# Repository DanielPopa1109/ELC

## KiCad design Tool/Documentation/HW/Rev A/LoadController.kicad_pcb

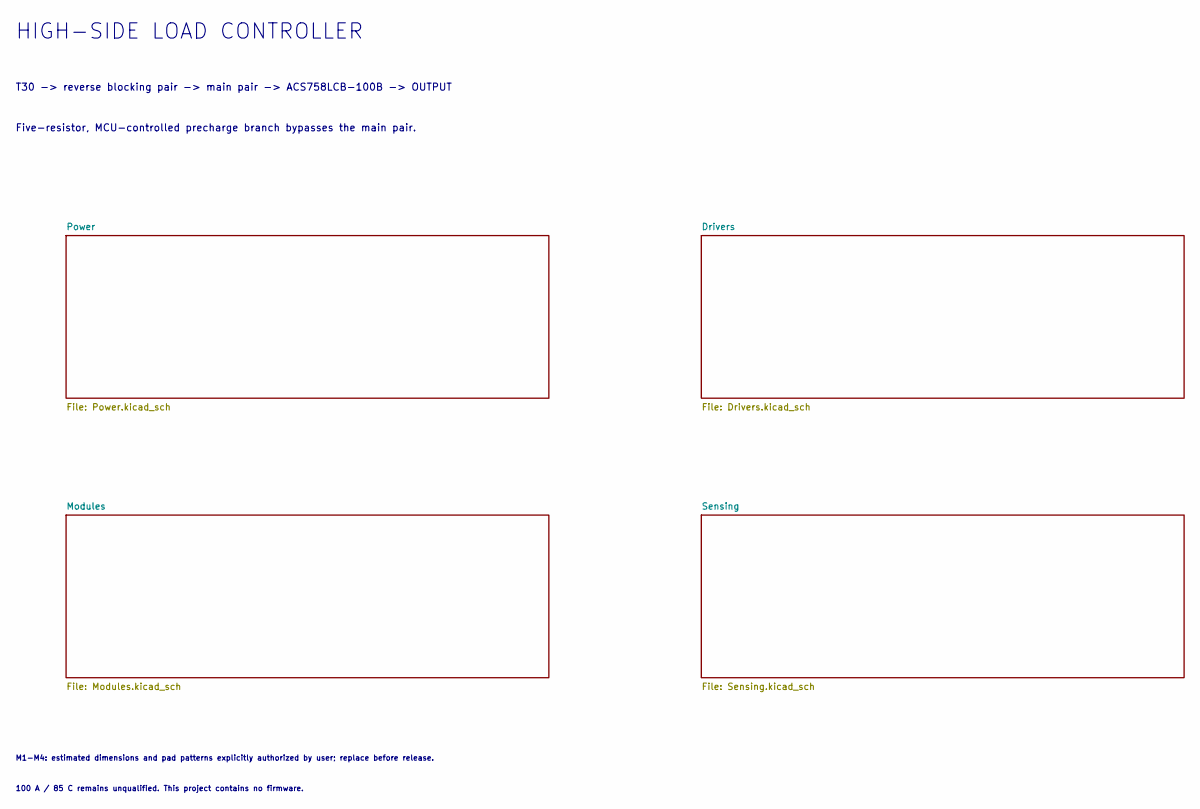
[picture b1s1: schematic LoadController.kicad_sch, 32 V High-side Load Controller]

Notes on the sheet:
Five-resistor, MCU-controlled precharge branch bypasses the main pair.
T30 -> reverse blocking pair -> main pair -> ACS758LCB-100B -> OUTPUT
100 A / 85 C remains unqualified. This project contains no firmware.
M1-M4: estimated dimensions and pad patterns explicitly authorized by user; replace before release.
HIGH-SIDE LOAD CONTROLLER

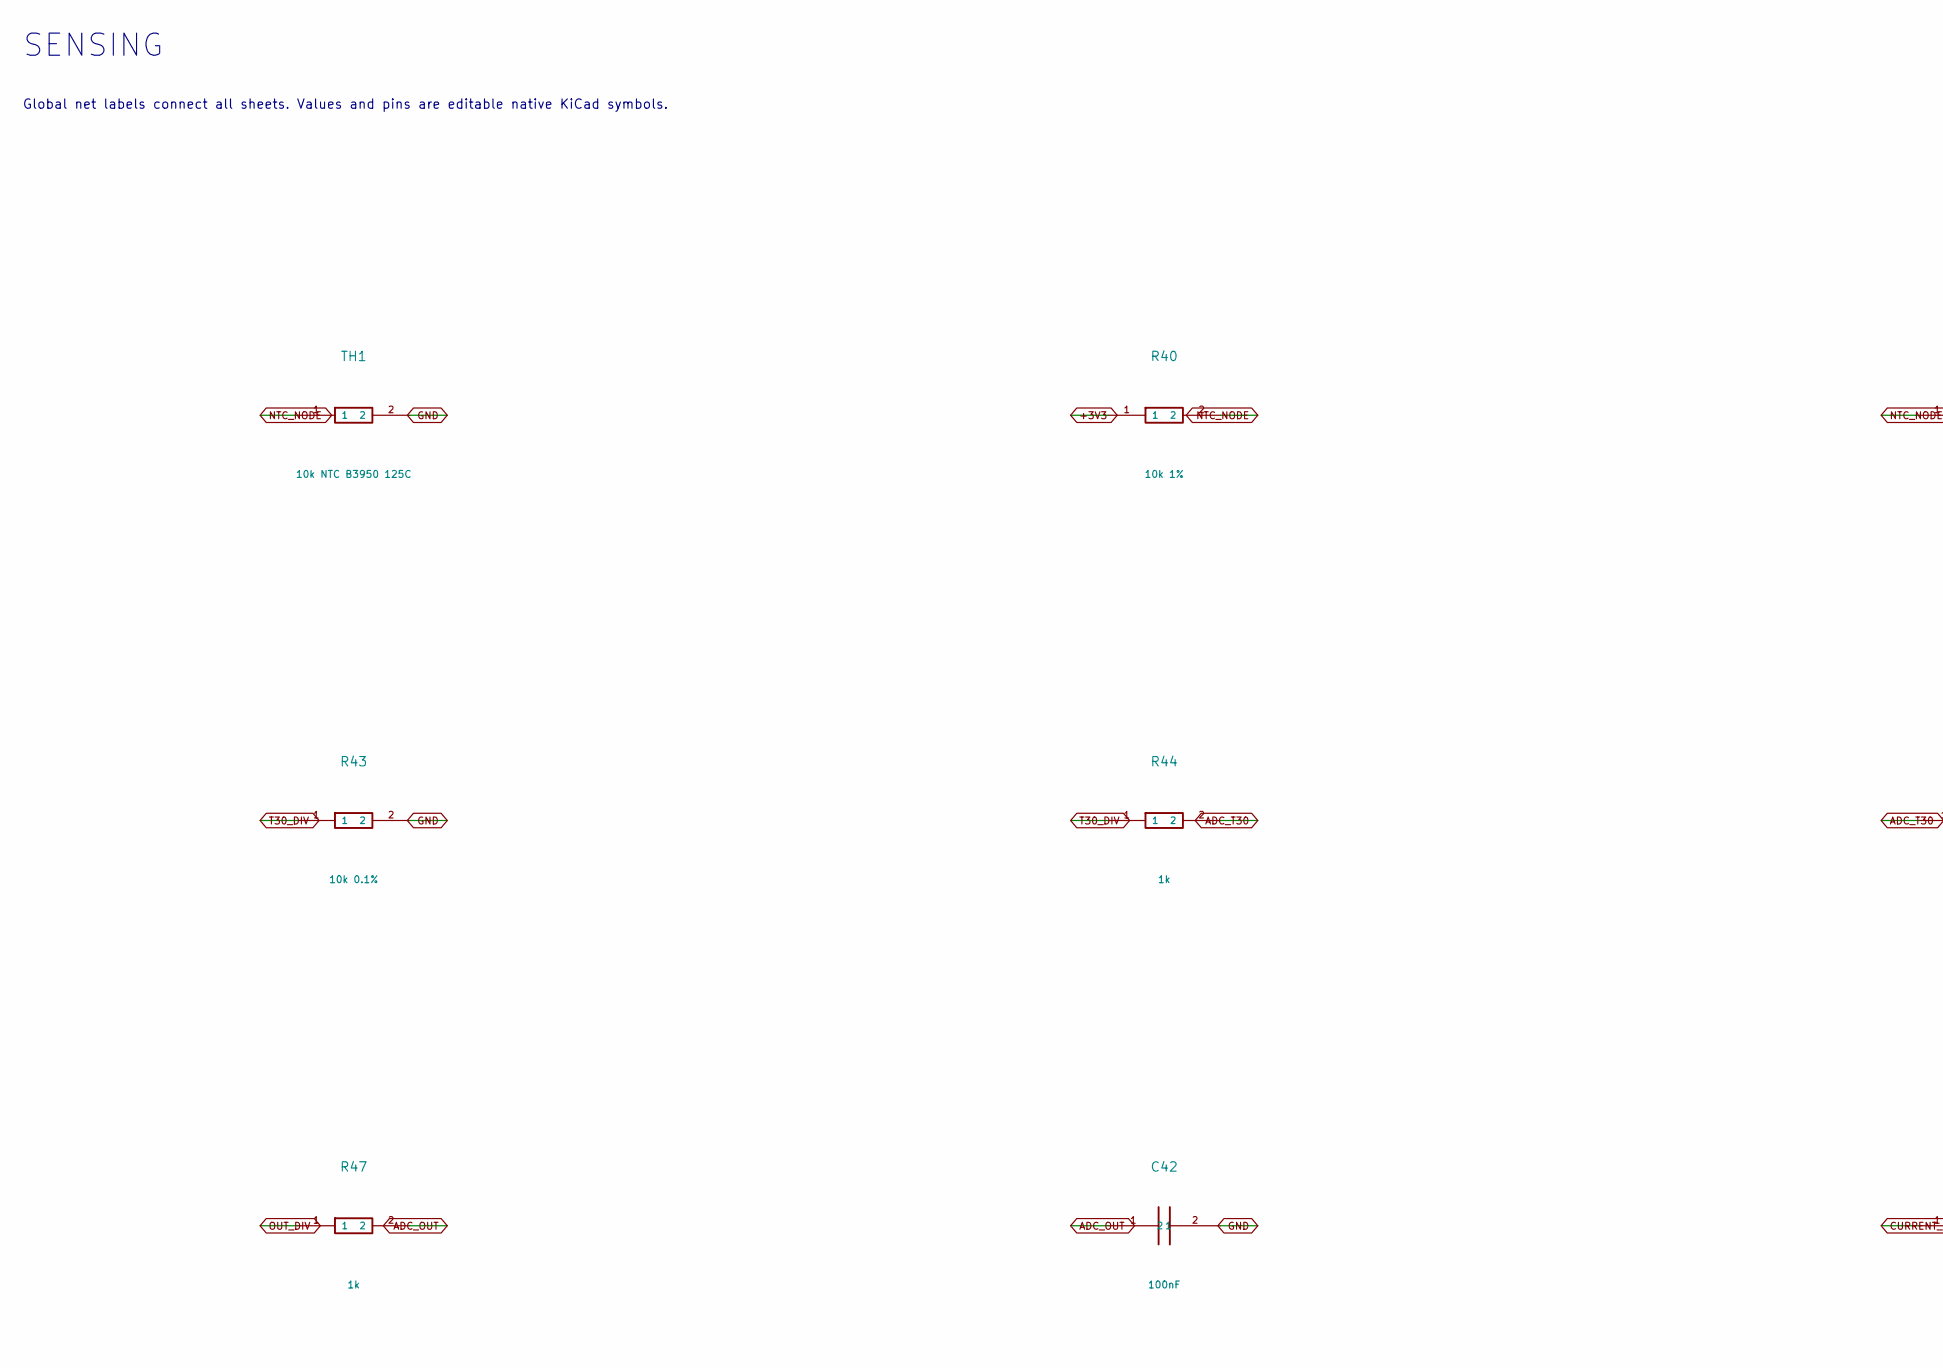
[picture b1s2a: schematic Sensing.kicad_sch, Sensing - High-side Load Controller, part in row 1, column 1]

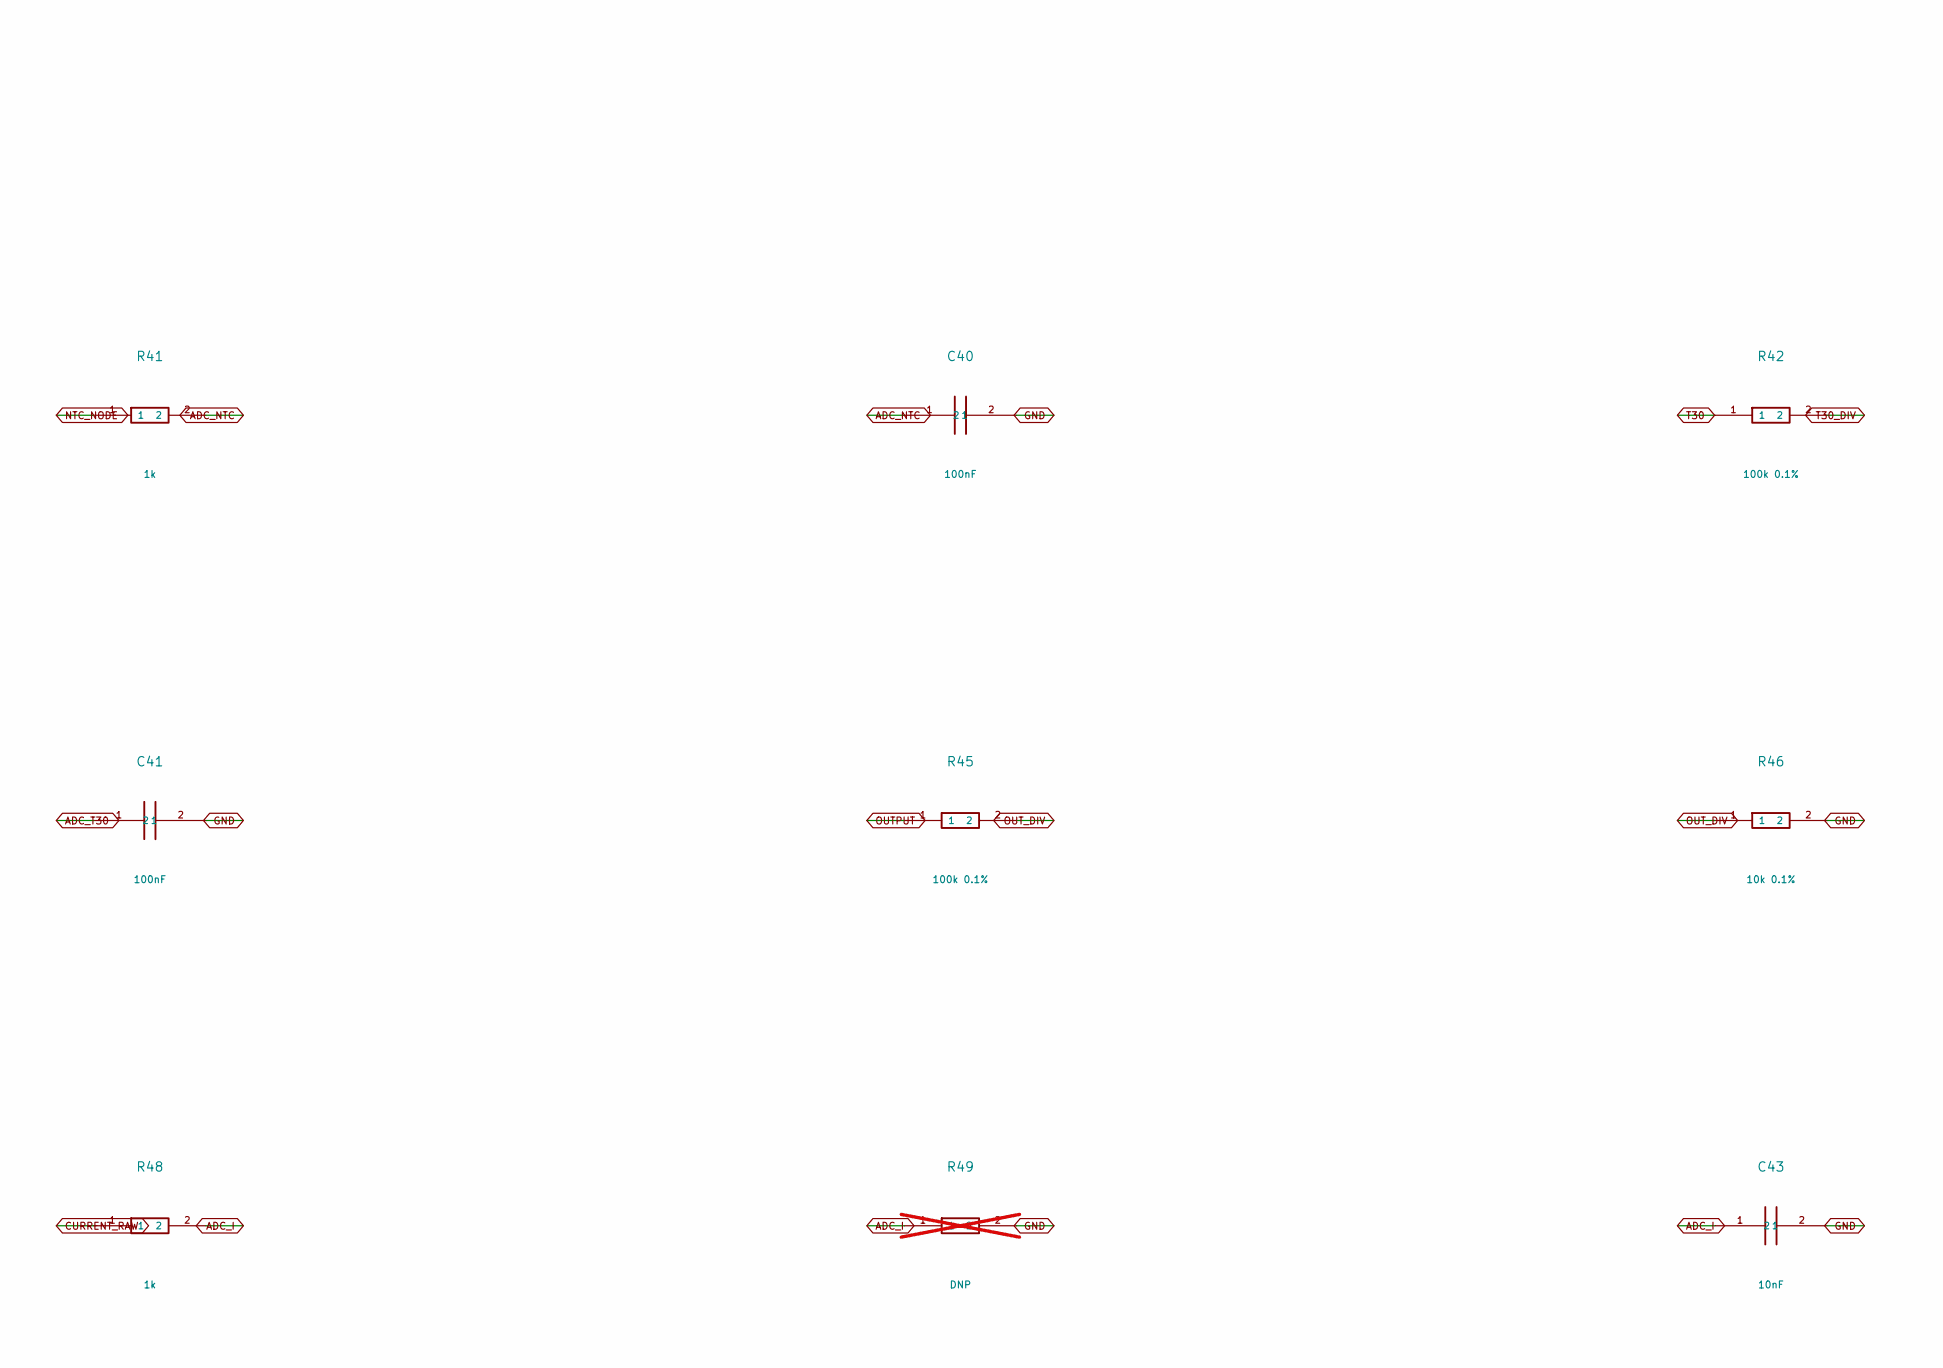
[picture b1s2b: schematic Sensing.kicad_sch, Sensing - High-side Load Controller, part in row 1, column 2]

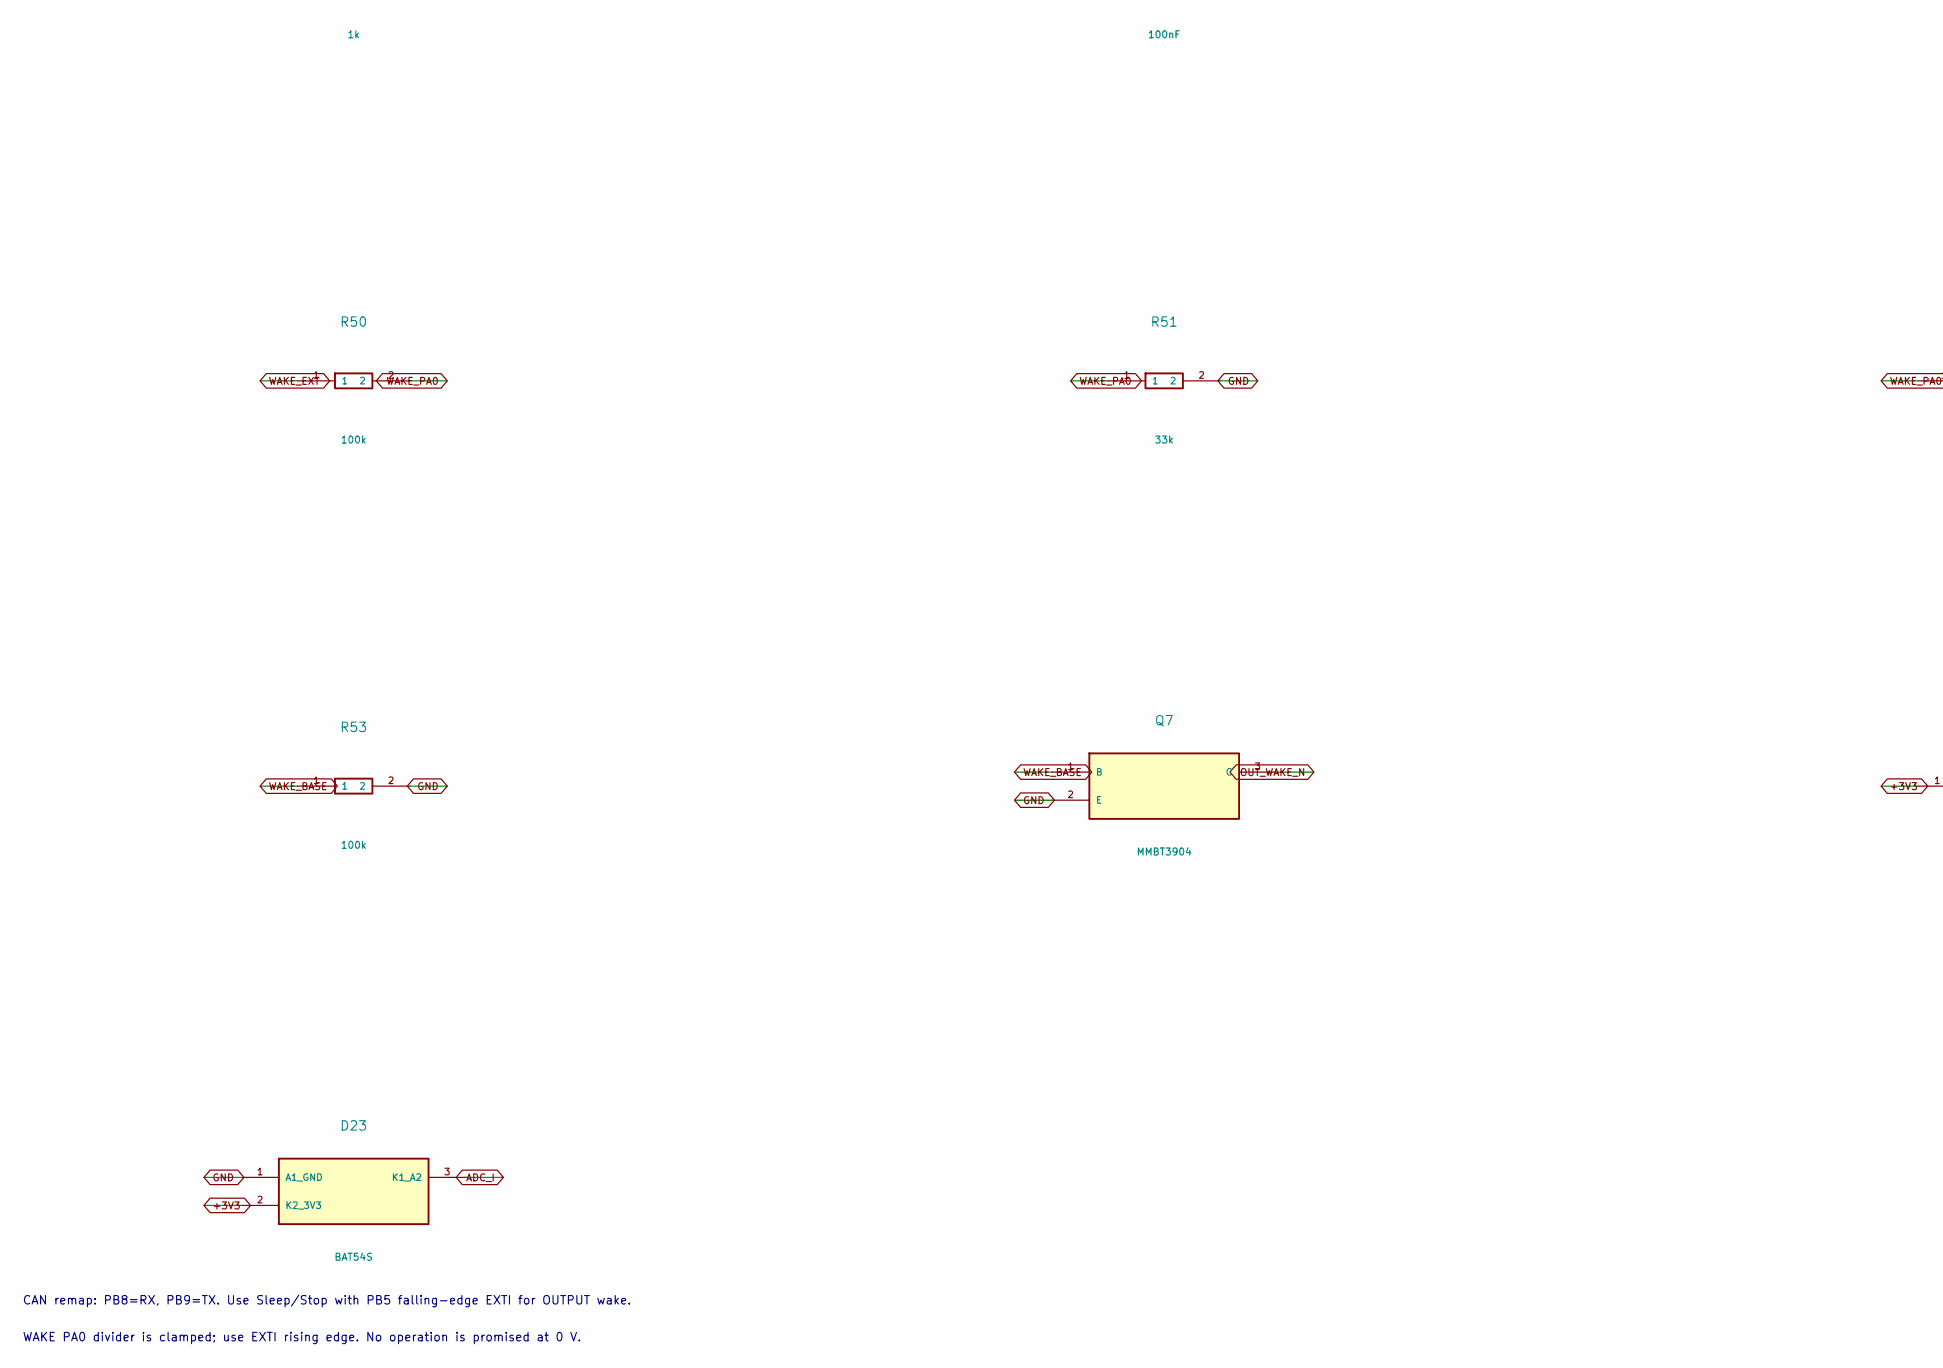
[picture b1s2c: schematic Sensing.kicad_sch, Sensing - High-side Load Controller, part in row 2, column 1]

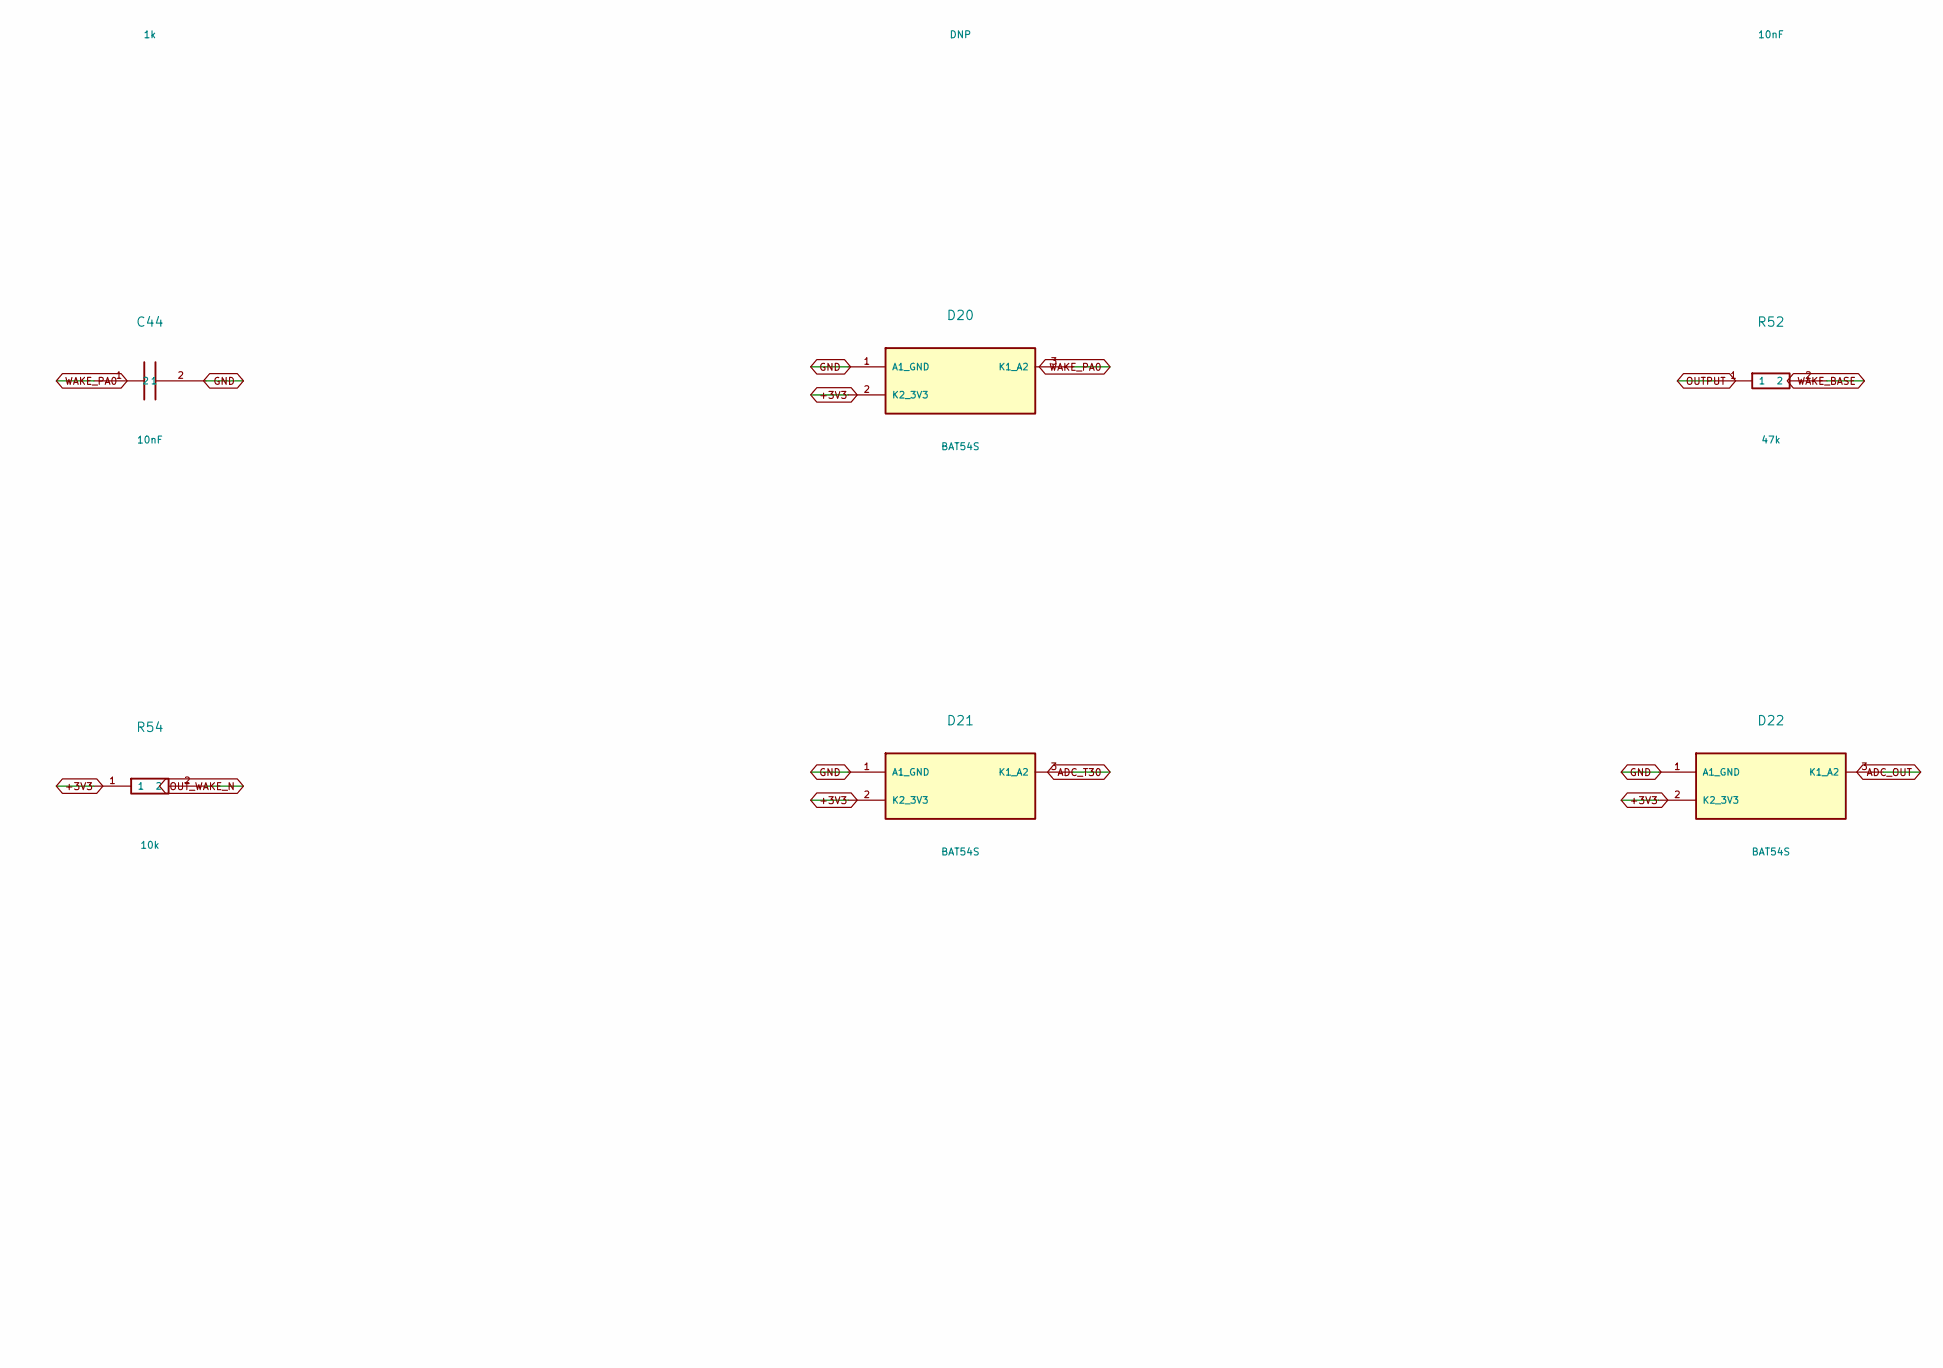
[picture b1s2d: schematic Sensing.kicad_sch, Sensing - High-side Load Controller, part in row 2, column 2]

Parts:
C40, C41, C42: 100nF; 0805
C43, C44: 10nF; 0805
D20, D21, D22, D23: BAT54S; SOT23
Q7: MMBT3904; SOT23
R40: 10k 1%; 0805
R41, R44, R47, R48: 1k; 0805
R42, R45: 100k 0.1%; 0805
R43, R46: 10k 0.1%; 0805
R49: DNP; 0805; not fitted
R50, R53: 100k; 0805
R51: 33k; 0805
R52: 47k; 0805
R54: 10k; 0805
TH1: 10k NTC B3950 125C; 0805

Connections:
+3V3: D20.2 (K2_3V3), D21.2 (K2_3V3), D22.2 (K2_3V3), D23.2 (K2_3V3), R40.1, R54.1; also elsewhere on the board
ADC_I: C43.1, D23.3 (K1_A2), R48.2, R49.1; also elsewhere on the board
ADC_NTC: C40.1, R41.2; also elsewhere on the board
ADC_OUT: C42.1, D22.3 (K1_A2), R47.2; also elsewhere on the board
ADC_T30: C41.1, D21.3 (K1_A2), R44.2; also elsewhere on the board
CURRENT_RAW: R48.1; also elsewhere on the board
GND: C40.2, C41.2, C42.2, C43.2, C44.2, D20.1 (A1_GND), D21.1 (A1_GND), D22.1 (A1_GND), D23.1 (A1_GND), Q7.2 (E), R43.2, R46.2, R49.2, R51.2, R53.2, TH1.2; also elsewhere on the board
NTC_NODE: R40.2, R41.1, TH1.1
OUTPUT: R45.1, R52.1; also elsewhere on the board
OUT_DIV: R45.2, R46.1, R47.1
OUT_WAKE_N: Q7.3 (C), R54.2; also elsewhere on the board
T30: R42.1; also elsewhere on the board
T30_DIV: R42.2, R43.1, R44.1
WAKE_BASE: Q7.1 (B), R52.2, R53.1
WAKE_EXT: R50.1; also elsewhere on the board
WAKE_PA0: C44.1, D20.3 (K1_A2), R50.2, R51.1; also elsewhere on the board

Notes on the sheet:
Global net labels connect all sheets. Values and pins are editable native KiCad symbols.
CAN remap: PB8=RX, PB9=TX. Use Sleep/Stop with PB5 falling-edge EXTI for OUTPUT wake.
SENSING
WAKE PA0 divider is clamped; use EXTI rising edge. No operation is promised at 0 V.
